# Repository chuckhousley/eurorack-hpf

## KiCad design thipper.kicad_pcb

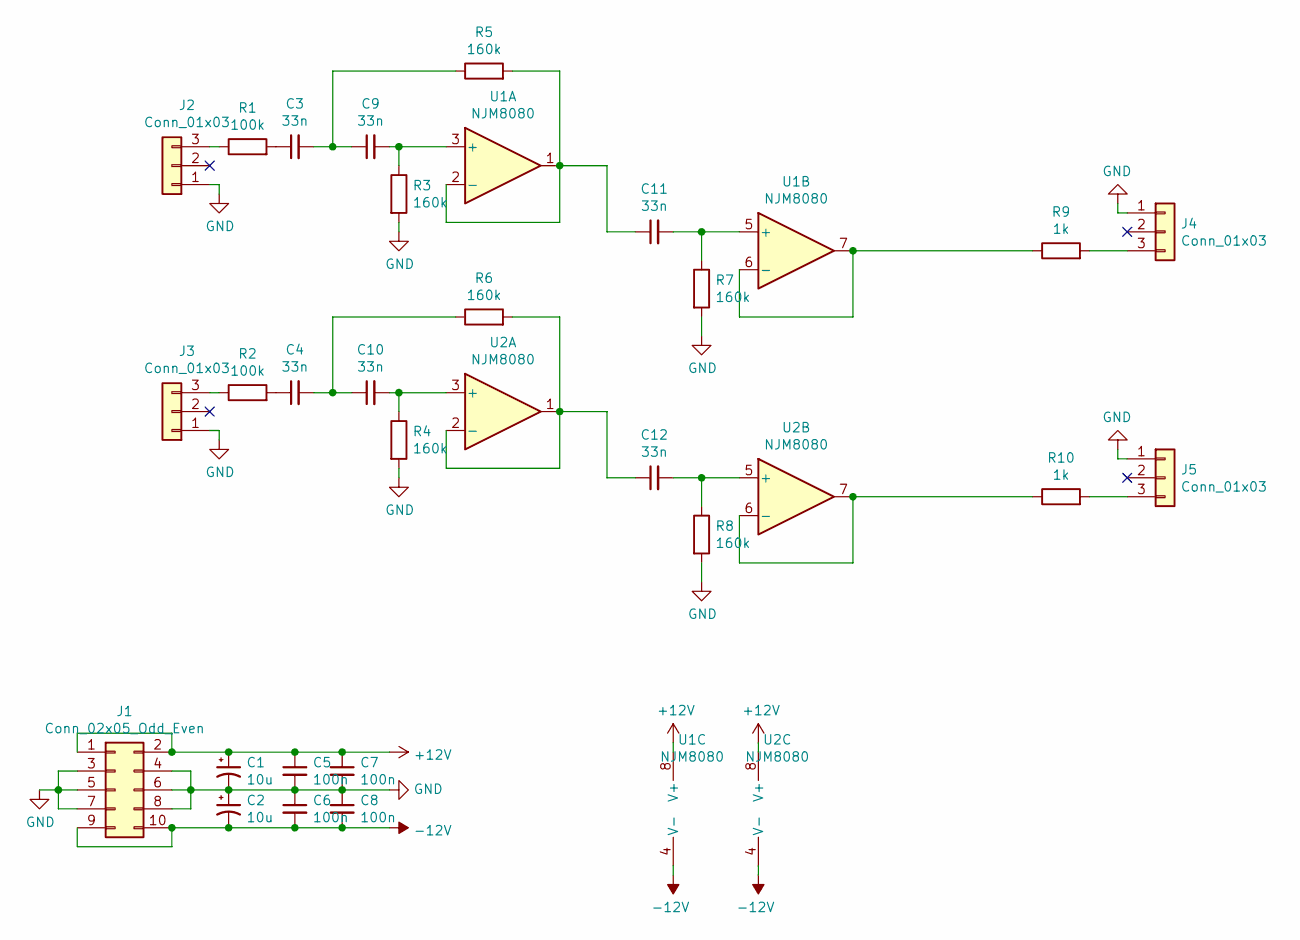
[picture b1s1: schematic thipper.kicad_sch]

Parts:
C1, C2: 10u; CP_Elec_4x5.4
C3, C4, C9, C10, C11, C12: 33n; C_0805_2012Metric_Pad1.15x1.40mm_HandSolder
C5, C6, C7, C8: 100n; C_0805_2012Metric_Pad1.15x1.40mm_HandSolder
J1: Conn_02x05_Odd_Even; Euro_Header_10-pin_TH
J2, J3, J4, J5: Conn_01x03; THONKICONN
R1, R2: 100k; R_0805_2012Metric_Pad1.15x1.40mm_HandSolder
R3, R4, R5, R6, R7, R8: 160k; R_0805_2012Metric_Pad1.15x1.40mm_HandSolder
R9, R10: 1k; R_0805_2012Metric_Pad1.15x1.40mm_HandSolder
U1, U2: NJM8080; SOP-8_3.9x4.9mm_P1.27mm

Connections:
+12V: C1.1, C5.1, C7.1, J1.1, J1.2, U1.8 (V+), U2.8 (V+)
-12V: C2.2, C6.2, C8.2, J1.9, J1.10, U1.4 (V-), U2.4 (V-)
GND: C1.2, C2.1, C5.2, C6.1, C7.2, C8.1, J1.3, J1.4, J1.5, J1.6, J1.7, J1.8, J2.1, J3.1, J4.1, J5.1, R3.2, R4.2, R7.2, R8.2
unnamed: C3.1, R1.2
unnamed: C3.2, C9.1, R5.1
unnamed: C4.1, R2.2
unnamed: C9.2, R3.1, U1.3 (+)
unnamed: C4.2, C10.1, R6.1
unnamed: C10.2, R4.1, U2.3 (+)
unnamed: C11.1, R5.2, U1.1, U1.2 (-)
unnamed: C11.2, R7.1, U1.5 (+)
unnamed: C12.1, R6.2, U2.1, U2.2 (-)
unnamed: C12.2, R8.1, U2.5 (+)
unnamed: J2.3, R1.1
unnamed: J3.3, R2.1
unnamed: J4.3, R9.2
unnamed: J5.3, R10.2
unnamed: R9.1, U1.6 (-), U1.7
unnamed: R10.1, U2.6 (-), U2.7

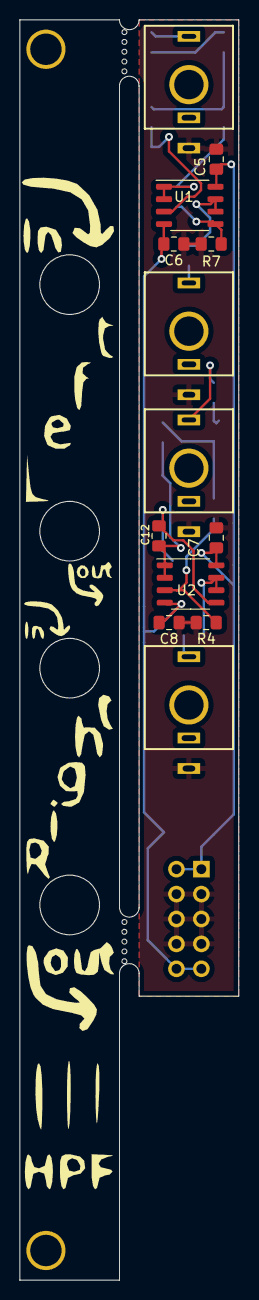
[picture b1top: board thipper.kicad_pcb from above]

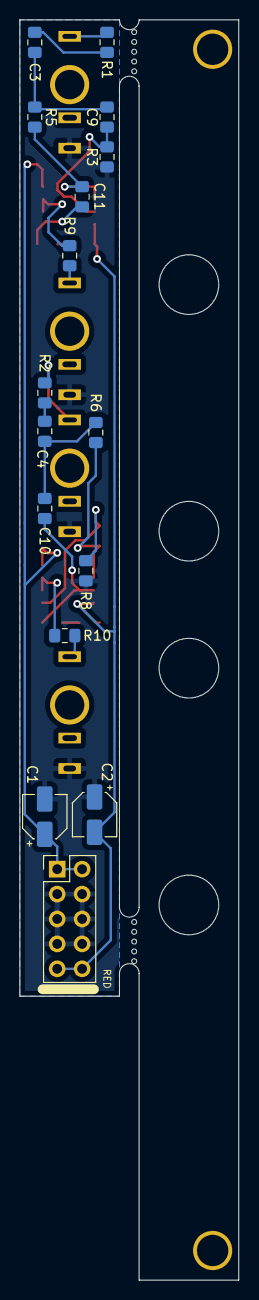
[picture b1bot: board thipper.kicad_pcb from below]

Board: 2 copper layers, 22.3 x 128.5 mm, 31 parts (16 on the bottom side), 19 nets.

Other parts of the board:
MOUSEBITE1mm, MOUSEBITE1mm#2: VAL**; MOUSEBITE1mm
